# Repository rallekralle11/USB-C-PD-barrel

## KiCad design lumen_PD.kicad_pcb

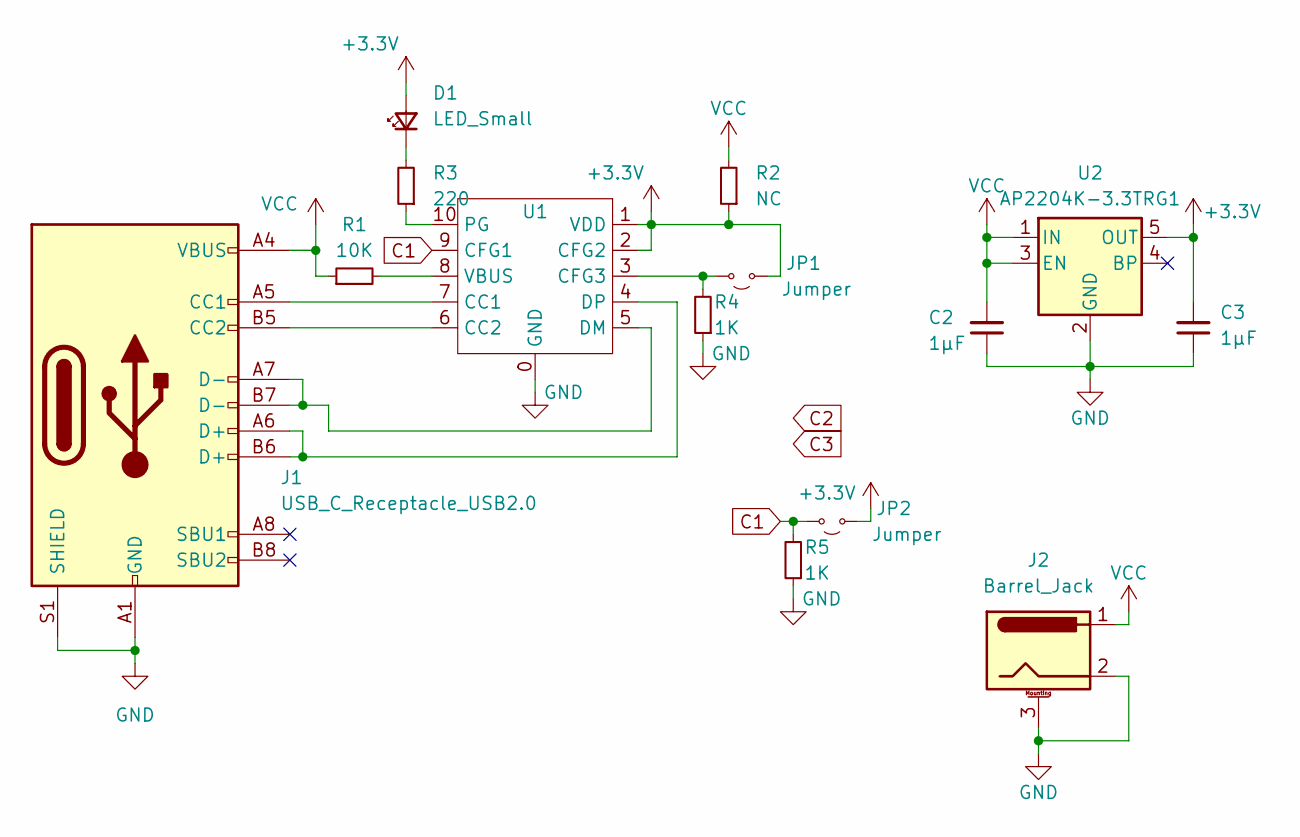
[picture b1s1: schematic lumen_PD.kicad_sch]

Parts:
C2, C3: 1µF; C_0402_1005Metric
D1: LED_Small; LED_0402_1005Metric
J1: USB_C_Receptacle_USB2.0; USB_C_Receptacle_G-Switch_GT-USB-7010ASV
J2: Barrel_Jack; BarrelJack_Horizontal
JP1, JP2: Jumper; SolderJumper-2_P1.3mm_Open_RoundedPad1.0x1.5mm
R1: 10K; R_0402_1005Metric
R2: NC; R_0402_1005Metric
R3: 220; R_0402_1005Metric
R4, R5: 1K; R_0402_1005Metric
U1: SOIC-10_3.9x4.9mm_P1mm
U2: AP2204K-3.3TRG1; SOT-23-5

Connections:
+3.3V: C3.2, D1.2 (A), JP1.1 (A), JP2.1 (A), R2.1, U1.1 (VDD), U1.2 (CFG2), U2.5 (OUT)
C1: JP2.2 (B), R5.2, U1.9 (CFG1)
GND: C2.1, C3.1, J1.A1 (GND), J1.A12 (GND), J1.B1 (GND), J1.B12 (GND), J1.S1 (SHIELD), J2.2, J2.3 (MountPin), R4.1, R5.1, U1.0 (GND), U2.2 (GND)
unnamed: D1.1 (K), R3.2
unnamed: J1.A5 (CC1), U1.7 (CC1)
unnamed: J1.B5 (CC2), U1.6 (CC2)
unnamed: JP1.2 (B), R4.2, U1.3 (CFG3)
unnamed: J1.A7 (D-), J1.B7 (D-), U1.5 (DM)
unnamed: J1.A6 (D+), J1.B6 (D+), U1.4 (DP)
unnamed: R3.1, U1.10 (PG)
unnamed: R1.2, U1.8 (VBUS)
VCC: C2.2, J1.A4 (VBUS), J1.A9 (VBUS), J1.B4 (VBUS), J1.B9 (VBUS), J2.1, R1.1, R2.2, U2.1 (IN), U2.3 (EN)

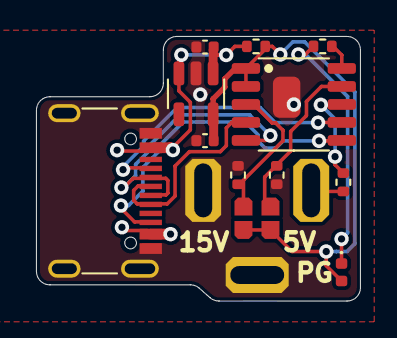
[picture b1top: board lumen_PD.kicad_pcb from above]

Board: 2 copper layers, 18.0 x 14.7 mm, 14 parts (0 on the bottom side), 12 nets.

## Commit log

2024-11-20 init
2024-12-06 finishing i guess
